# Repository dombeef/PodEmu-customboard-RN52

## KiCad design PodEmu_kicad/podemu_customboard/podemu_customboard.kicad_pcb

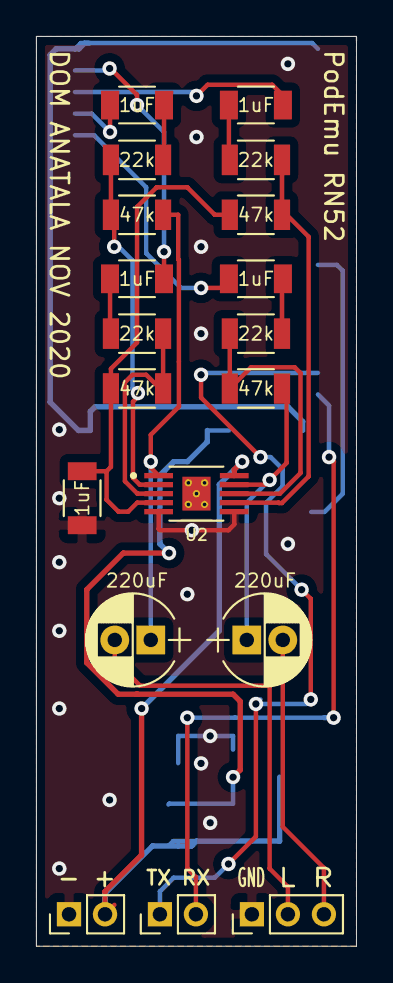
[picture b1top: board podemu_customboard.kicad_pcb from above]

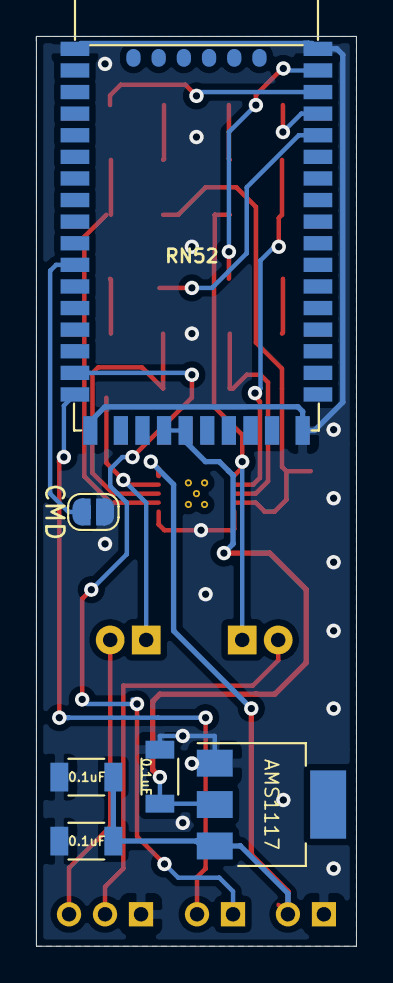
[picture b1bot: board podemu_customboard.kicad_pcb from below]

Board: 2 copper layers, 17.8 x 50.5 mm, 25 parts (6 on the bottom side), 23 nets.

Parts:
0.1uF, 0.1uF#2: 0.1uF; C_1206
220uF, 220uF#2: 220uF; CP_Radial_D5.0mm_P2.00mm
- +: PWR_-_+; Pin_Header_Straight_1x02_Pitch2.00mm
AMS1117: AMS1117-3.3; SOT-223
C3: 0.1uF; C_1206
C4, C5, C6, C7, C8: 1uF; C_1206
CMD: CMD_MODE; SolderJumper-2_P1.3mm_Open_RoundedPad1.0x1.5mm
L R: AUDIO_OUT_GND_L_R; Pin_Header_Straight_1x03_Pitch2.00mm
R1, R2, R3, R4: 22k; R_1206
R5, R6, R7, R8: 47k; R_1206
RN52: RN52-I_RM(50P-26X13.5MM); LGA50-1.0-26X13.5MM
TX RX: UART_TX_RX; Pin_Header_Straight_1x02_Pitch2.00mm
U2: TPA6112A2DGQR; IC_XTR111AIDGQR

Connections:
+3V3: AMS1117.2, C3.1, RN52.21, RN52.22
+5V: 0.1uF.1, 0.1uF#2.1, - +.2, AMS1117.3, U2.10
GND: 0.1uF.2, 0.1uF#2.2, - +.1, AMS1117.1, C3.2, C8.2, CMD.2, L R.1, RN52.1, RN52.18, RN52.27, RN52.44, U2.5, U2.6
unnamed: CMD.1, RN52.11
unnamed: RN52.16, TX RX.1
unnamed: RN52.17, TX RX.2
unnamed: C7.2, RN52.40
unnamed: C6.2, RN52.41
unnamed: C5.2, RN52.42
unnamed: C4.2, RN52.43
unnamed: C4.1, R1.2
unnamed: C5.1, R2.2
unnamed: C6.1, R3.2
unnamed: C7.1, R4.2
unnamed: C8.1, R6.1, R8.1, U2.4
unnamed: 220uF.1, R7.2, U2.9
unnamed: 220uF.2, L R.3
unnamed: 220uF#2.1, R5.2, U2.1
unnamed: 220uF#2.2, L R.2
unnamed: R1.1, R6.2, U2.3
unnamed: R2.1, R8.2, U2.7
unnamed: R3.1, R5.1, U2.2
unnamed: R4.1, R7.1, U2.8

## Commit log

2020-11-17 first board version finished up
    might have to tweak it later
